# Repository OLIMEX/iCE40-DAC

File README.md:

# iCE40-DAC
Extension module for iCE40HX1K-EVB or iCE40HX8K-EVB.

Adds fast Digital-Analog-Converter (DAC) functionality to the main board.

You can effectively use up to 4 x iCE40-DAC with a single EVB board (or up to 2 x iCE40-DAC when you have iCE40-IO connected to the same bus).

You can use the exported PDFs to access the schematic or the bill of materials. 

We used the latest KiCad night builds to create the design. Please use a new version KiCad to open it. 

License information should be found in LICENSE.txt

## Hardware revision changes:

### Hardware revision A1

- Changed resistor changing R9 to 0R (down from 10k), this is done because EXTIO was not properly grounded leading to wrong levels

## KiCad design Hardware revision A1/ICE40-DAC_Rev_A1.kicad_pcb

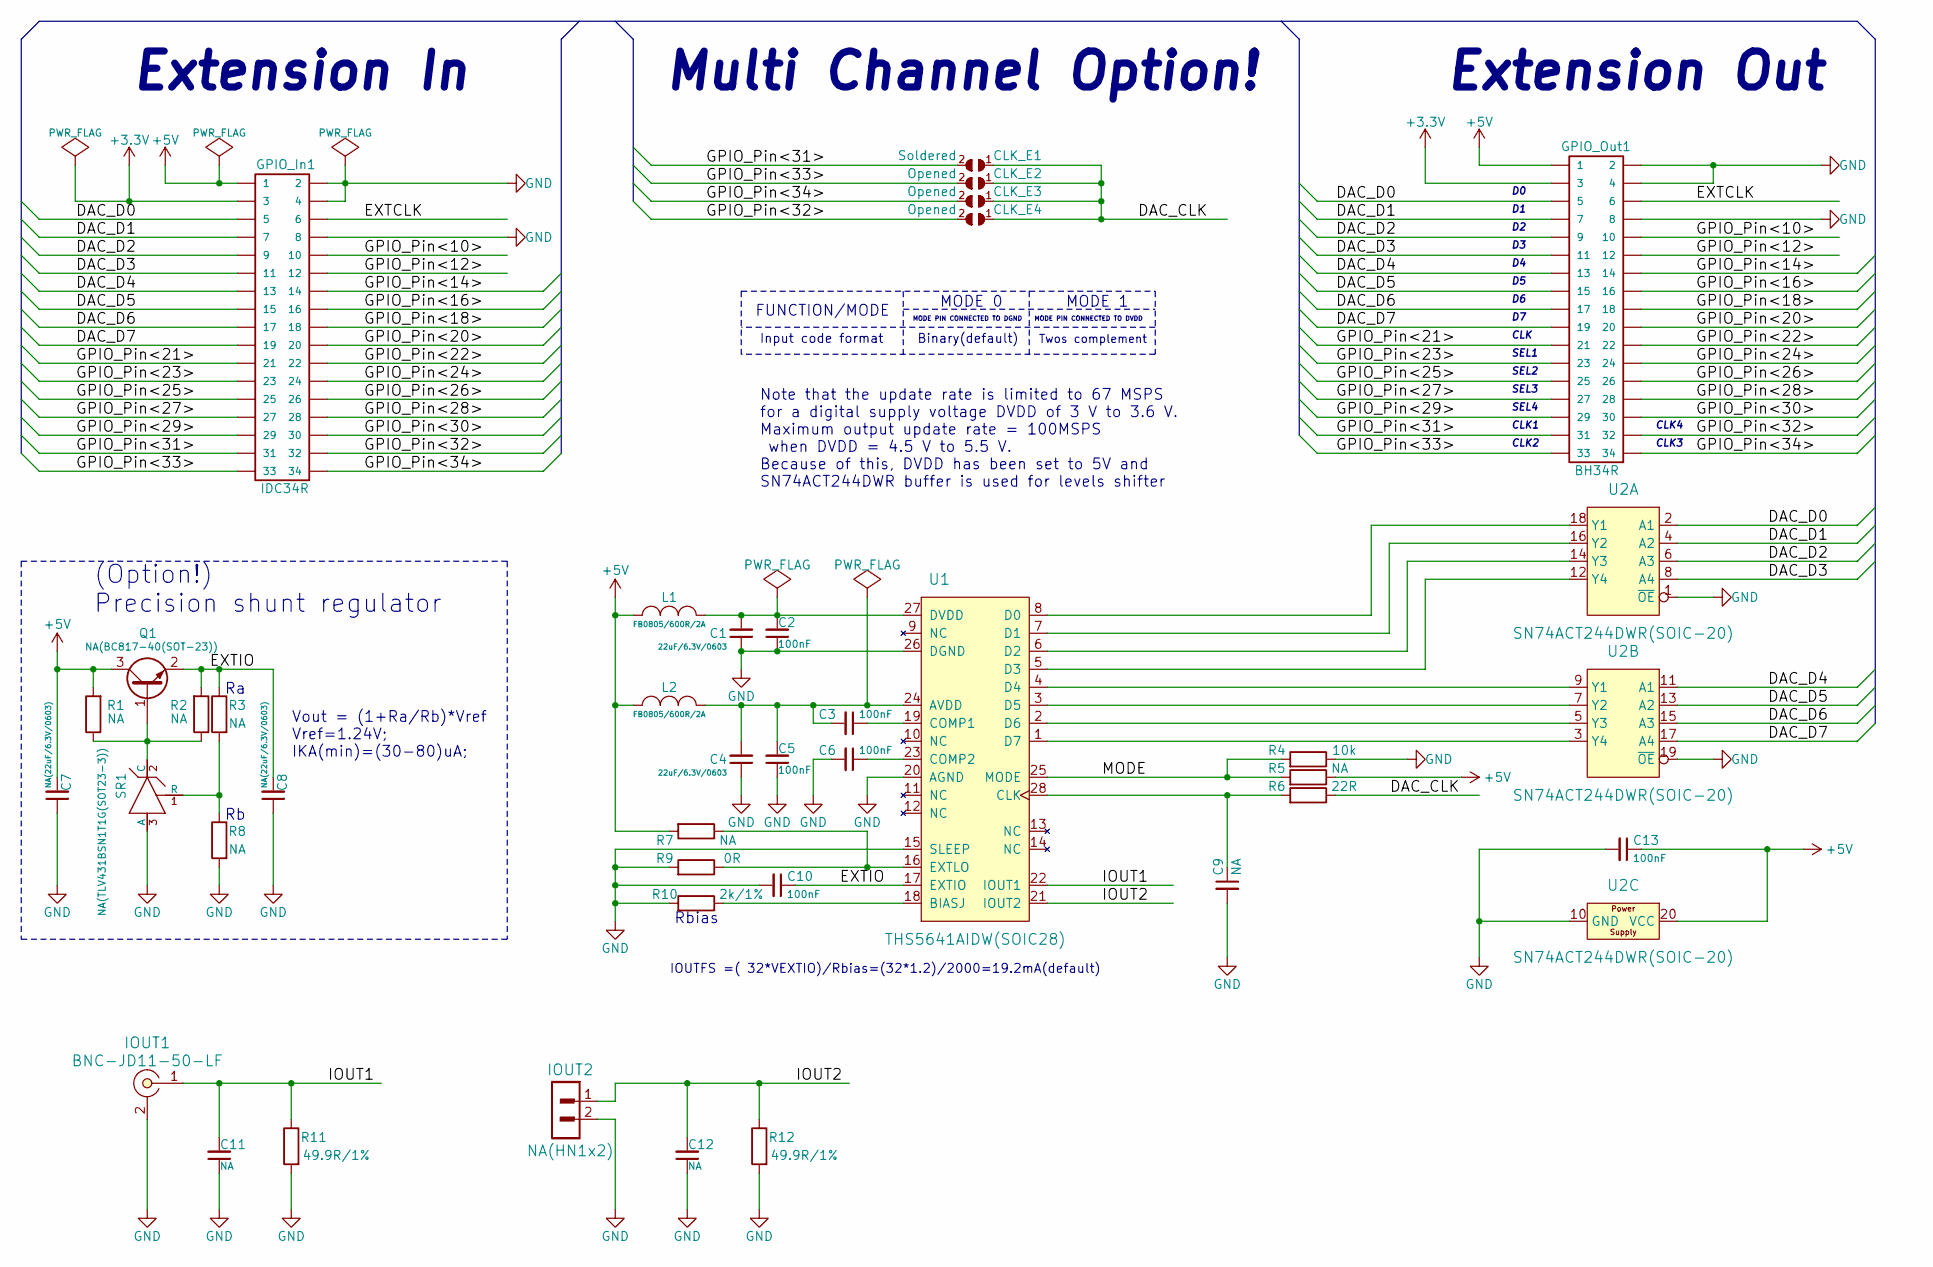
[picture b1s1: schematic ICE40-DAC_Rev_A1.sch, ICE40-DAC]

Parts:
C1, C4: 22uF/6.3V/0603; C_0603_5MIL_DWS
C2, C3, C5, C6, C10, C13: 100nF; C_0402_5MIL_DWS
C7, C8: NA(22uF/6.3V/0603); C_0603_5MIL_DWS
C9, C11, C12: NA; C_0402_5MIL_DWS
CLK_E1: Soldered; SJ
CLK_E2, CLK_E3, CLK_E4: Opened; SJ
GPIO_In1: IDC34R; IDC34R_PCB
GPIO_Out1: BH34R
IOUT1: BNC-JD11-50-LF; BNC-JD11-50-LF_1-IN_2-GND
IOUT2: NA(HN1x2); HN1x2
L1, L2: FB0805/600R/2A; L_0805_5MIL_DWS
Q1: NA(BC817-40(SOT-23)); SOT23
R1, R2, R3, R5, R7, R8: NA; R_0402_5MIL_DWS
R4: 10k; R_0402_5MIL_DWS
R6: 22R; R_0402_5MIL_DWS
R9: 0R; R_0402_5MIL_DWS
R10: 2k/1%; R_0402_5MIL_DWS
R11, R12: 49.9R/1%; R_0603_5MIL_DWS
SR1: NA(TLV431BSN1T1G(SOT23-3)); SOT-23
U1: THS5641AIDW(SOIC28); SOIC28-300
U2: SN74ACT244DWR(SOIC-20); SOIC20_300mil

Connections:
+3V3: GPIO_In1.3, GPIO_Out1.3
+5V: C7.2, C13.1, GPIO_In1.1, GPIO_Out1.1, L1.2, L2.1, Q1.3 (C), R1.2, R5.1, R7.2, U2.20 (VCC)
/DAC_CLK: CLK_E1.1, CLK_E2.1, CLK_E3.1, CLK_E4.1, R6.1
/DAC_D0: GPIO_In1.5, GPIO_Out1.5, U2.2 (A1)
/DAC_D1: GPIO_In1.7, GPIO_Out1.7, U2.4 (A2)
/DAC_D2: GPIO_In1.9, GPIO_Out1.9, U2.6 (A3)
/DAC_D3: GPIO_In1.11, GPIO_Out1.11, U2.8 (A4)
/DAC_D4: GPIO_In1.13, GPIO_Out1.13, U2.11 (A1)
/DAC_D5: GPIO_In1.15, GPIO_Out1.15, U2.13 (A2)
/DAC_D6: GPIO_In1.17, GPIO_Out1.17, U2.15 (A3)
/DAC_D7: GPIO_In1.19, GPIO_Out1.19, U2.17 (A4)
/EXTCLK: GPIO_In1.6, GPIO_Out1.6
/EXTIO: C8.2, C10.1, Q1.2 (E), R2.2, R3.1, U1.17 (EXTIO)
/GPIO_Pin<10>: GPIO_In1.10, GPIO_Out1.10
/GPIO_Pin<12>: GPIO_In1.12, GPIO_Out1.12
/GPIO_Pin<14>: GPIO_In1.14, GPIO_Out1.14
/GPIO_Pin<16>: GPIO_In1.16, GPIO_Out1.16
/GPIO_Pin<18>: GPIO_In1.18, GPIO_Out1.18
/GPIO_Pin<20>: GPIO_In1.20, GPIO_Out1.20
/GPIO_Pin<21>: GPIO_In1.21, GPIO_Out1.21
/GPIO_Pin<22>: GPIO_In1.22, GPIO_Out1.22
/GPIO_Pin<23>: GPIO_In1.23, GPIO_Out1.23
/GPIO_Pin<24>: GPIO_In1.24, GPIO_Out1.24
/GPIO_Pin<25>: GPIO_In1.25, GPIO_Out1.25
/GPIO_Pin<26>: GPIO_In1.26, GPIO_Out1.26
/GPIO_Pin<27>: GPIO_In1.27, GPIO_Out1.27
/GPIO_Pin<28>: GPIO_In1.28, GPIO_Out1.28
/GPIO_Pin<29>: GPIO_In1.29, GPIO_Out1.29
/GPIO_Pin<30>: GPIO_In1.30, GPIO_Out1.30
/GPIO_Pin<31>: CLK_E1.2, GPIO_In1.31, GPIO_Out1.31
/GPIO_Pin<32>: CLK_E4.2, GPIO_In1.32, GPIO_Out1.32
/GPIO_Pin<33>: CLK_E2.2, GPIO_In1.33, GPIO_Out1.33
/GPIO_Pin<34>: CLK_E3.2, GPIO_In1.34, GPIO_Out1.34
/IOUT1: C11.2, IOUT1.1, R11.1, U1.22 (IOUT1)
/IOUT2: C12.2, IOUT2.1, R12.1, U1.21 (IOUT2)
/MODE: R4.2, R5.2, U1.25 (MODE)
GND: C1.1, C2.1, C4.1, C5.1, C6.2, C7.1, C8.1, C9.2, C10.2, C11.1, C12.1, C13.2, GPIO_In1.2, GPIO_In1.4, GPIO_In1.8, GPIO_Out1.2, GPIO_Out1.4, GPIO_Out1.8, IOUT1.2, IOUT2.2, R4.1, R8.2, R9.2, R10.2, R11.2, R12.2, SR1.3 (A), U1.15 (SLEEP), U1.20 (AGND), U1.26 (DGND), U2.1 (~OE), U2.10 (GND), U2.19 (~OE)
unnamed: C1.2, C2.2, L1.1, U1.27 (DVDD)
unnamed: C3.1, U1.19 (COMP1)
unnamed: C3.2, C4.2, C5.2, L2.2, U1.24 (AVDD)
unnamed: C6.1, U1.23 (COMP2)
unnamed: C9.1, R6.2, U1.28 (CLK)
unnamed: Q1.1 (B), R1.1, R2.1, SR1.2 (C)
unnamed: R3.2, R8.1, SR1.1 (R)
unnamed: R7.1, R9.1, U1.16 (EXTLO)
unnamed: R10.1, U1.18 (BIASJ)
unnamed: U1.1 (D7), U2.3 (Y4)
unnamed: U1.2 (D6), U2.5 (Y3)
unnamed: U1.3 (D5), U2.7 (Y2)
unnamed: U1.4 (D4), U2.9 (Y1)
unnamed: U1.5 (D3), U2.12 (Y4)
unnamed: U1.6 (D2), U2.14 (Y3)
unnamed: U1.7 (D1), U2.16 (Y2)
unnamed: U1.8 (D0), U2.18 (Y1)

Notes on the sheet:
Extension Out
Extension In
Vout = (1+Ra/Rb)*Vref Vref=1.24V; IKA(min)=(30-80)uA;
(Option!) Precision shunt regulator
Multi Channel Option!
CLK
SEL1
SEL2
SEL3
SEL4
Note that the update rate is limited to 67 MSPS for a digital supply voltage DVDD of 3 V to 3.6 V. Maximum output update rate = 100MSPS when DVDD = 4.5 V to 5.5 V. Because of this, DVDD has been set to 5V and SN74ACT244DWR buffer is used for levels shifter
Rbias
IOUTFS =( 32*VEXTIO)/Rbias=(32*1.2)/2000=19.2mA(default)
FUNCTION/MODE
MODE 0
MODE 1
MODE PIN CONNECTED TO DGND
MODE PIN CONNECTED TO DVDD
Input code format
Binary(default)
Twos complement
CLK1
CLK2
CLK3
CLK4

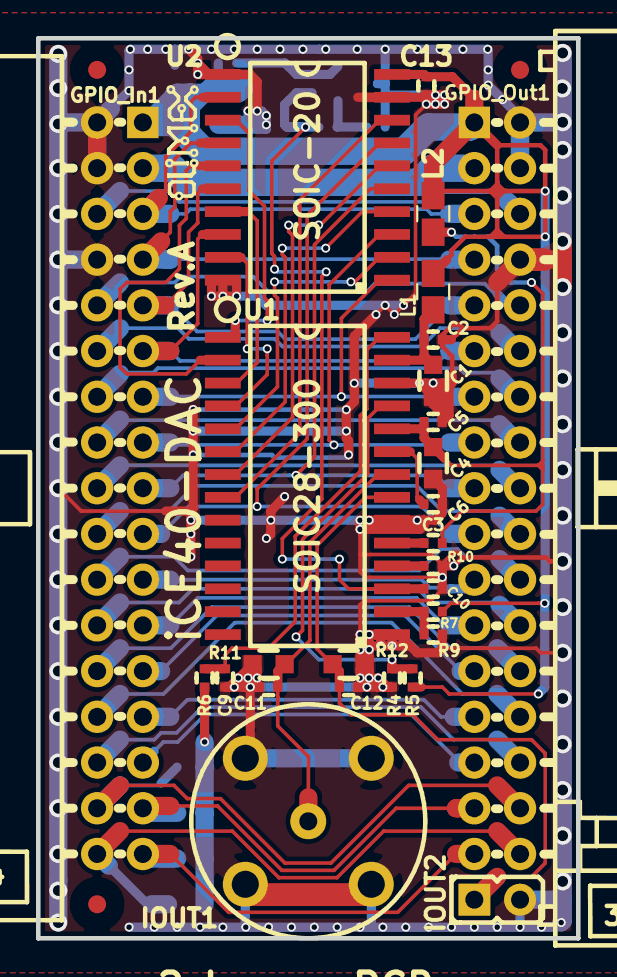
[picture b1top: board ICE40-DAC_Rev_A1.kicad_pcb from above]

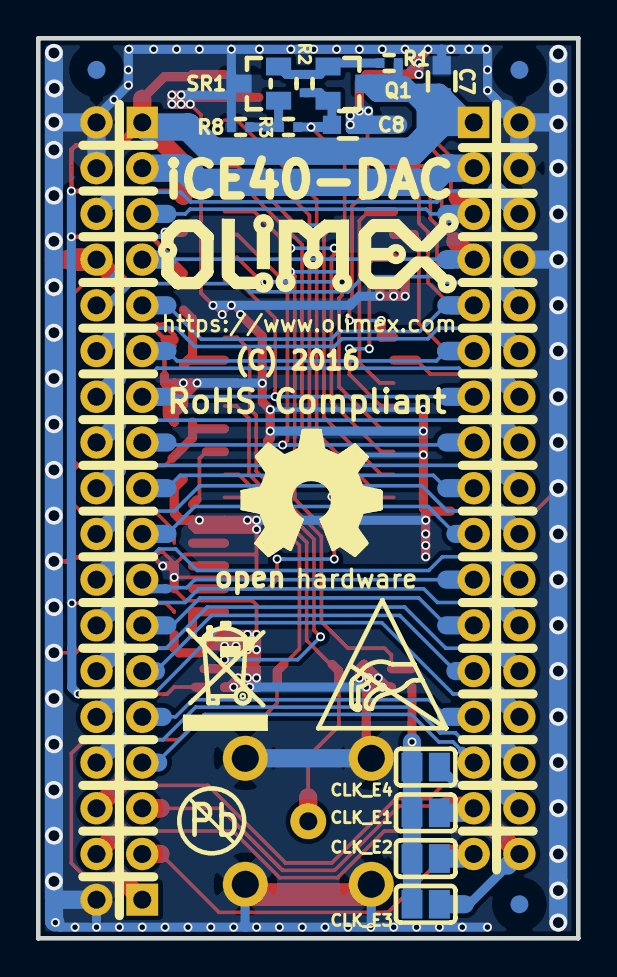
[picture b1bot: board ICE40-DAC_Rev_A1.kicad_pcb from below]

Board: 2 copper layers, 30.0 x 50.0 mm, 40 parts (13 on the bottom side), 54 nets.

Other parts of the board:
Ref**: Val**; LOGO_ANTISTATIC_1

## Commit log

2017-07-11 :tada: Added .gitattributes & .gitignore files
2017-07-11 Update
    relocate
2017-07-11 Update
    Updated trace names
2017-07-11 Create LICENSE
2021-04-07 update
    revision A1 and 3d added

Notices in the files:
Hardware revision A1/ICE40-DAC_Rev_A1.kicad_pcb:
(C) 2016
